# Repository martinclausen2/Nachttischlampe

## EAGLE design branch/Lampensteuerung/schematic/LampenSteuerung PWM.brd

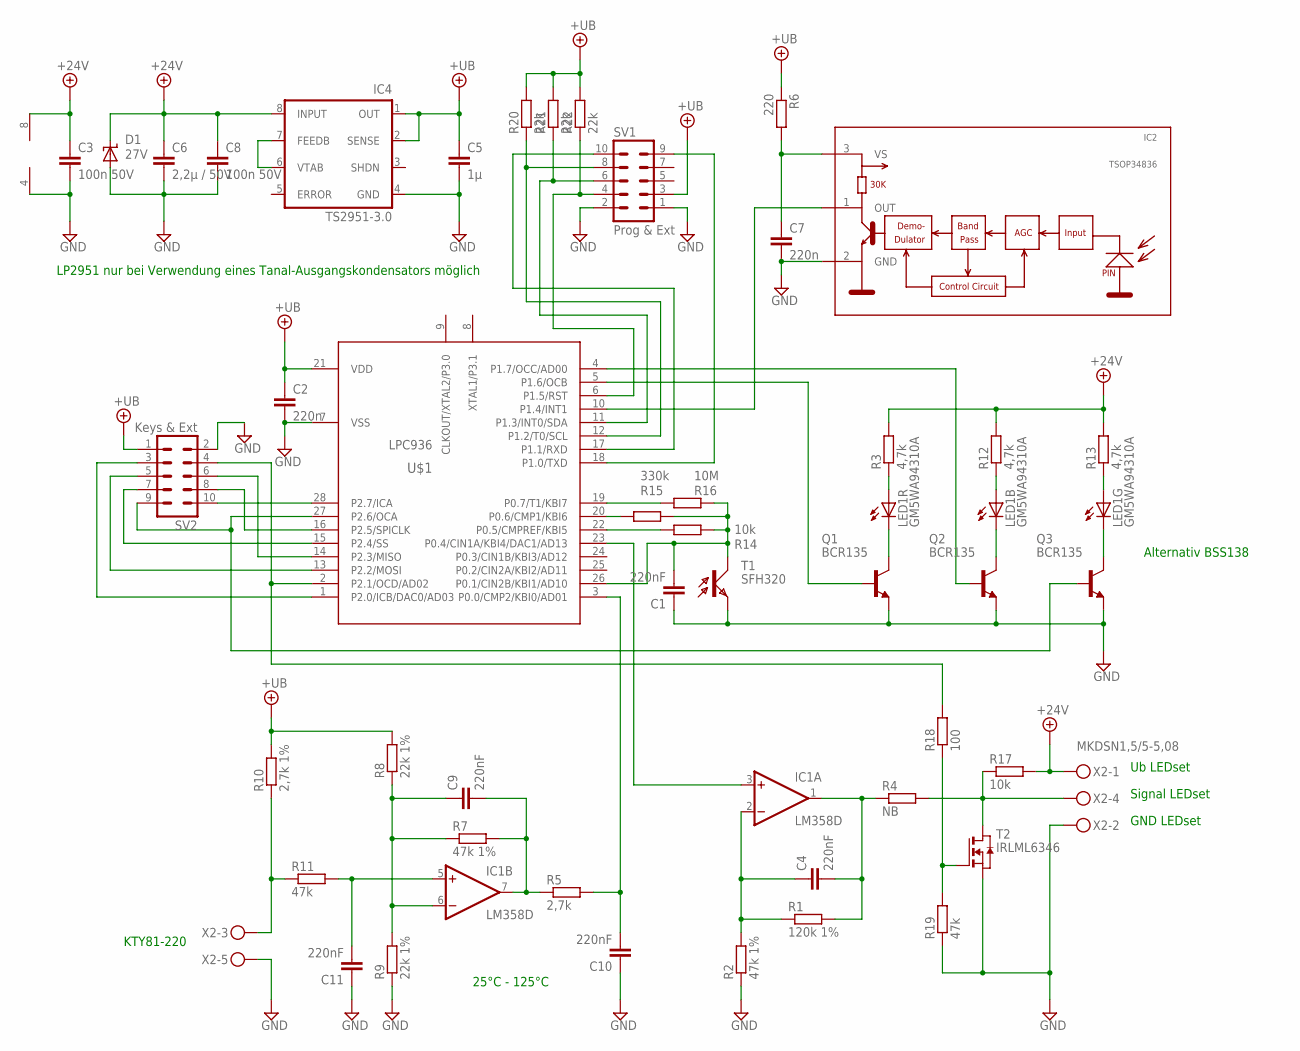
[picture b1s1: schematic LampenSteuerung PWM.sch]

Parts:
C1, C4, C9, C10, C11: 220nF; C0603
C2, C7: 220n; C0603
C3, C8: 100n 50V; C0603
C5: 1µ; C0805
C6: 2,2µ / 50V; C1206
D1: 27V; SMBJ
IC1: LM358D; SO08
IC2: TSOP34836; TSOP348
IC4: TS2951-3.0; SO-08
LED1: GM5WA94310A
Q1, Q2, Q3: BCR135; SOT23-BEC
R1: 120k 1%; R0805
R2, R7: 47k 1%; R0805
R3, R12, R13: 4,7k; R0805
R4: NB; R0805
R5: 2,7k; R0805
R6: 220; R0805
R8, R9: 22k 1%; R0805
R10: 2,7k 1%; R0805
R11, R19: 47k; R0805
R14, R17: 10k; R0805
R15: 330k; R0805
R16: 10M; R0805
R18: 100; R0805
R20, R21, R22: 22k; R0805
SV1: Prog & Ext; MA05-2
SV2: Keys & Ext; MA05-2
T1: SFH320; PLCC2
T2: IRLML6346; SOT-23
U$1: LPC936; TSSOP28
X2: MKDSN1,5/5-5,08

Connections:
+12V: C3.1, C6.1, C8.1, D1.C, IC1.8 (V+), IC4.8 (INPUT), R3.2, R12.2, R13.2, R17.2, X2.1
+UB: C2.1, C5.1, IC4.1 (OUT), IC4.2 (SENSE), R6.1, R8.2, R10.2, R20.2, R21.2, R22.2, SV1.3, SV2.1, U$1.21 (VDD)
GND: C1.1, C2.2, C3.2, C5.2, C6.2, C7.2, C8.2, C10.1, C11.1, D1.A, IC1.4 (V-), IC2.2 (GND), IC4.4 (GND), Q1.E, Q2.E, Q3.E, R2.1, R9.1, R19.1, SV1.1, SV1.2, SV2.2, T1.C (E), T2.2 (S), U$1.7 (VSS), X2.2, X2.5
unnamed: IC4.6 (VTAB), IC4.7 (FEEDB)
unnamed: IC2.1 (OUT), U$1.10 (P1.4/INT1)
unnamed: IC1.3 (+IN), U$1.23 (P0.4/CIN1A/KBI4/DAC1/AD13)
unnamed: C9.1, IC1.6 (-IN), R7.1, R8.1, R9.2
unnamed: LED1.5 (C), Q1.C
unnamed: C4.2, IC1.1 (OUT), R1.2, R4.1
unnamed: C4.1, IC1.2 (-IN), R1.1, R2.2
unnamed: SV1.10, U$1.17 (P1.1/RXD)
unnamed: R4.2, R17.1, T2.1 (D), X2.4
unnamed: C7.1, IC2.3 (VS), R6.2
unnamed: SV1.9, U$1.18 (P1.0/TXD)
unnamed: LED1.6 (C), Q2.C
unnamed: R22.1, SV1.4, U$1.6 (P1.5/RST)
unnamed: LED1.1 (A), R12.1
unnamed: R20.1, SV1.8, U$1.12 (P1.2/T0/SCL)
unnamed: R21.1, SV1.6, U$1.11 (P1.3/INT0/SDA)
unnamed: C10.2, R5.2, U$1.3 (P0.0/CMP2/KBI0/AD01)
unnamed: R10.1, R11.1, X2.3
unnamed: C9.2, IC1.7 (OUT), R5.1, R7.2
unnamed: C11.2, IC1.5 (+IN), R11.2
unnamed: LED1.2 (A), R3.1
unnamed: SV2.3, U$1.1 (P2.0/ICB/DAC0/AD03)
unnamed: R18.2, SV2.4, U$1.2 (P2.1/OCD/AD02)
unnamed: SV2.5, U$1.13 (P2.2/MOSI)
unnamed: SV2.6, U$1.14 (P2.3/MISO)
unnamed: SV2.7, U$1.15 (P2.4/SS)
unnamed: SV2.8, U$1.16 (P2.5/SPICLK)
unnamed: Q3.B, SV2.9, U$1.27 (P2.6/OCA)
unnamed: SV2.10, U$1.28 (P2.7/ICA)
unnamed: LED1.3 (A), R13.1
unnamed: LED1.4 (C), Q3.C
unnamed: Q1.B, U$1.5 (P1.6/OCB)
unnamed: Q2.B, U$1.4 (P1.7/OCC/AD00)
unnamed: C1.2, R14.1, R15.1, R16.1, T1.A (C), U$1.26 (P0.1/CIN2B/KBI1/AD10)
unnamed: R16.2, U$1.19 (P0.7/T1/KBI7)
unnamed: R15.2, U$1.20 (P0.6/CMP1/KBI6)
unnamed: R14.2, U$1.22 (P0.5/CMPREF/KBI5)
unnamed: R18.1, R19.2, T2.3 (G)

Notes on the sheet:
LP2951 nur bei Verwendung eines Tanal-Ausgangskondensators möglich
Signal LEDset
Ub LEDset
GND LEDset
KTY81-220
25°C - 125°C
Alternativ BSS138

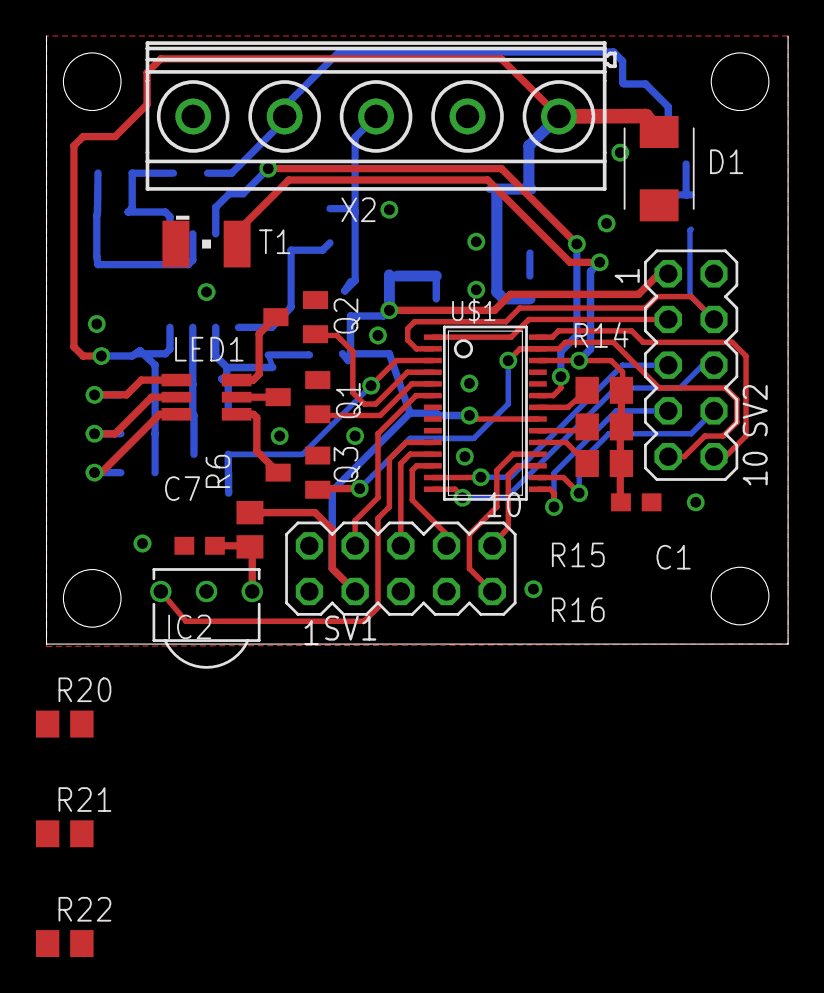
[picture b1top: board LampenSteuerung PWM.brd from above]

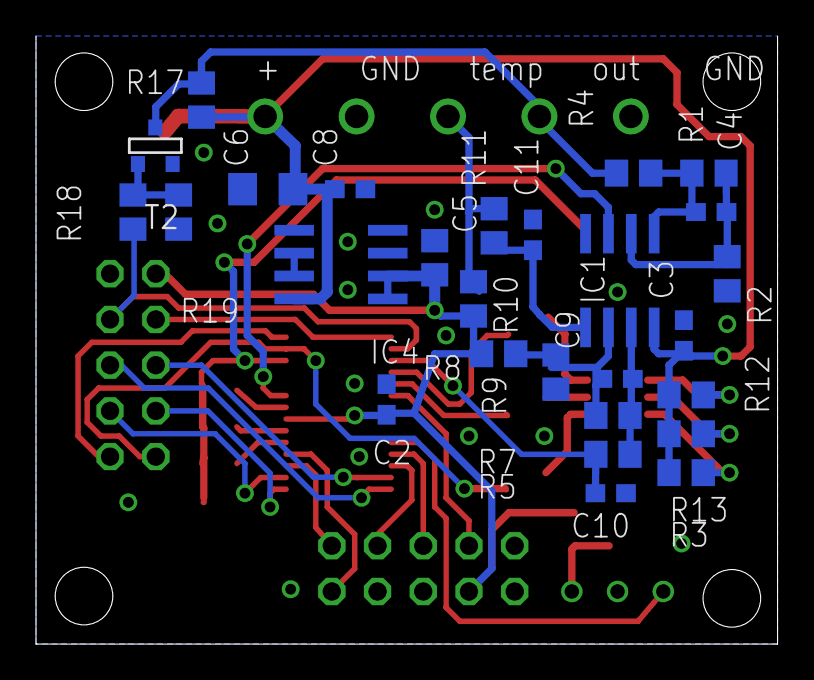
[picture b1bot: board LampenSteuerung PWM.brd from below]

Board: 2 copper layers, 41.2 x 33.8 mm, 47 parts (27 on the bottom side), 41 nets.

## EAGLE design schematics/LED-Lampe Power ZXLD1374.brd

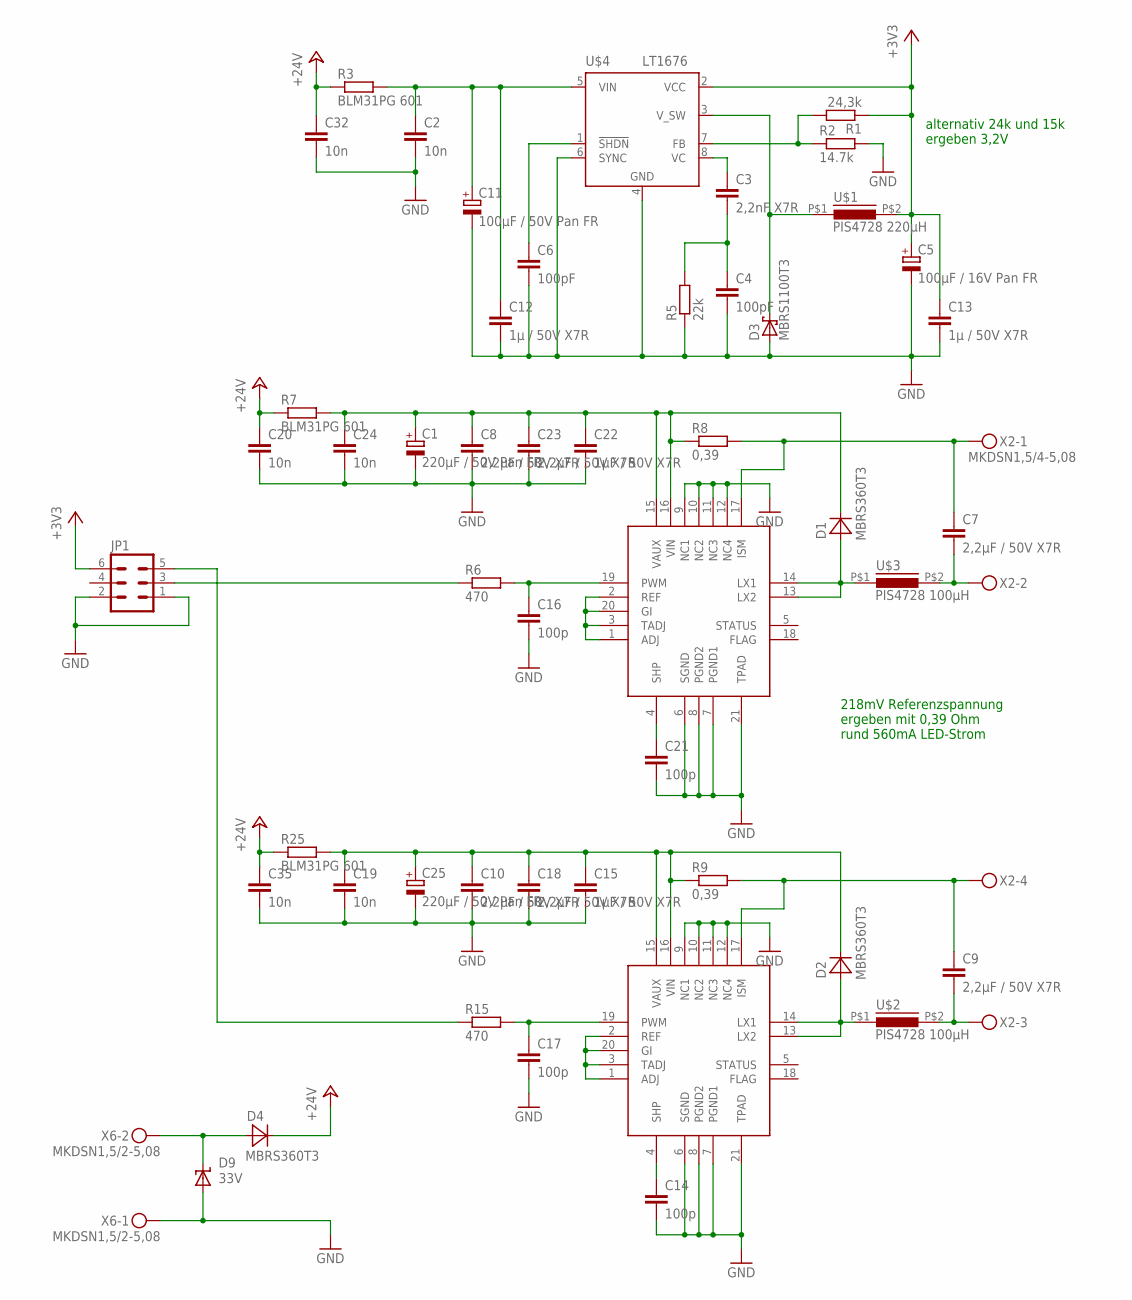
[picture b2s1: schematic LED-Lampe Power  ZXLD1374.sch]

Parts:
C1, C25: 220µF / 50V Pan FR; E5-10,5
C2, C19, C20, C24, C32, C35: 10n; C0805
C3: 2,2nF X7R; C0603
C4, C6: 100pF; C0603
C5: 100µF / 16V Pan FR; E2-5
C7, C8, C9, C10, C18, C23: 2,2µF / 50V X7R; C1206
C11: 100µF / 50V Pan FR; E3,5-8
C12, C13: 1µ / 50V X7R; C1206
C14, C16, C17, C21: 100p; C0603
C15, C22: 1µF / 50V X7R; C1206
D1, D2, D4: MBRS360T3; SMC
D3: MBRS1100T3; SMB
D9: 33V; SMBJ
JP1: ML6
R1: 24,3k; R1206
R2: 14.7k; R1206
R3, R7, R25: BLM31PG 601; R1206
R5: 22k; R1206
R6, R15: 470; R0805
R8, R9: 0,39; R1206
U$1: PIS4728 220µH; FASTON_PIS4728
U$2, U$3: PIS4728 100µH; FASTON_PIS4728
U$4: LT1676; S8
U$5, U$6: ZXLD1374; TSSOP20CA(FE)
X2: MKDSN1,5/4-5,08
X6: MKDSN1,5/2-5,08

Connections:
+3V3: C5.+, C13.1, JP1.6, R1.1, U$1.P$2 (2), U$4.2 (VCC); also elsewhere on the board
+24V: C20.1, C32.1, C35.1, D4.C, R3.1, R7.1, R25.1
GND: C1.-, C2.2, C4.2, C5.-, C6.2, C8.2, C10.2, C11.-, C12.2, C13.2, C14.2, C15.2, C16.2, C17.2, C18.2, C19.2, C20.2, C21.2, C22.2, C23.2, C24.2, C25.-, C32.2, C35.2, D3.A, D9.A, JP1.1, JP1.2, R2.2, R5.1, U$4.4 (GND), U$4.6 (SYNC), U$5.6 (SGND), U$5.7 (PGND1), U$5.8 (PGND2), U$5.9 (NC1), U$5.10 (NC2), U$5.11 (NC3), U$5.12 (NC4), U$5.21 (TPAD), U$6.6 (SGND), U$6.7 (PGND1), U$6.8 (PGND2), U$6.9 (NC1), U$6.10 (NC2), U$6.11 (NC3), U$6.12 (NC4), U$6.21 (TPAD), X6.1
unnamed: C2.1, C11.+, C12.1, R3.2, U$4.5 (VIN)
unnamed: U$5.1 (ADJ), U$5.2 (REF), U$5.3 (TADJ), U$5.20 (GI)
unnamed: C3.2, C4.1, R5.2
unnamed: R1.2, R2.1, U$4.7 (FB)
unnamed 7: D3.C, U$1.P$1 (1), U$4.3 (V_SW); also elsewhere on the board
unnamed: JP1.3, R6.1
unnamed: C1.+, C8.1, C22.1, C23.1, C24.1, D1.C, R7.2, R8.1, U$6.15 (VAUX), U$6.16 (VIN)
unnamed: D4.A, D9.C, X6.2
unnamed: C3.1, U$4.8 (VC)
unnamed 12: C9.2, U$2.P$2 (2), X2.3; also elsewhere on the board
unnamed: C17.1, R15.2, U$5.19 (PWM)
unnamed: C6.1, U$4.1 (!SHDN)
unnamed: C9.1, R9.2, U$5.17 (ISM), X2.4
unnamed: C14.1, U$5.4 (SHP)
unnamed 17: D2.A, U$2.P$1 (1), U$5.13 (LX2), U$5.14 (LX1); also elsewhere on the board
unnamed: C16.1, R6.2, U$6.19 (PWM)
unnamed 19: C7.2, U$3.P$2 (2), X2.2; also elsewhere on the board
unnamed: C7.1, R8.2, U$6.17 (ISM), X2.1
unnamed: U$6.1 (ADJ), U$6.2 (REF), U$6.3 (TADJ), U$6.20 (GI)
unnamed: C21.1, U$6.4 (SHP)
unnamed 23: D1.A, U$3.P$1 (1), U$6.13 (LX2), U$6.14 (LX1); also elsewhere on the board
unnamed: C10.1, C15.1, C18.1, C19.1, C25.+, D2.C, R9.1, R25.2, U$5.15 (VAUX), U$5.16 (VIN)
P1.6: JP1.5, R15.1

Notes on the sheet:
218mV Referenzspannung ergeben mit 0,39 Ohm rund 560mA LED-Strom
alternativ 24k und 15k ergeben 3,2V

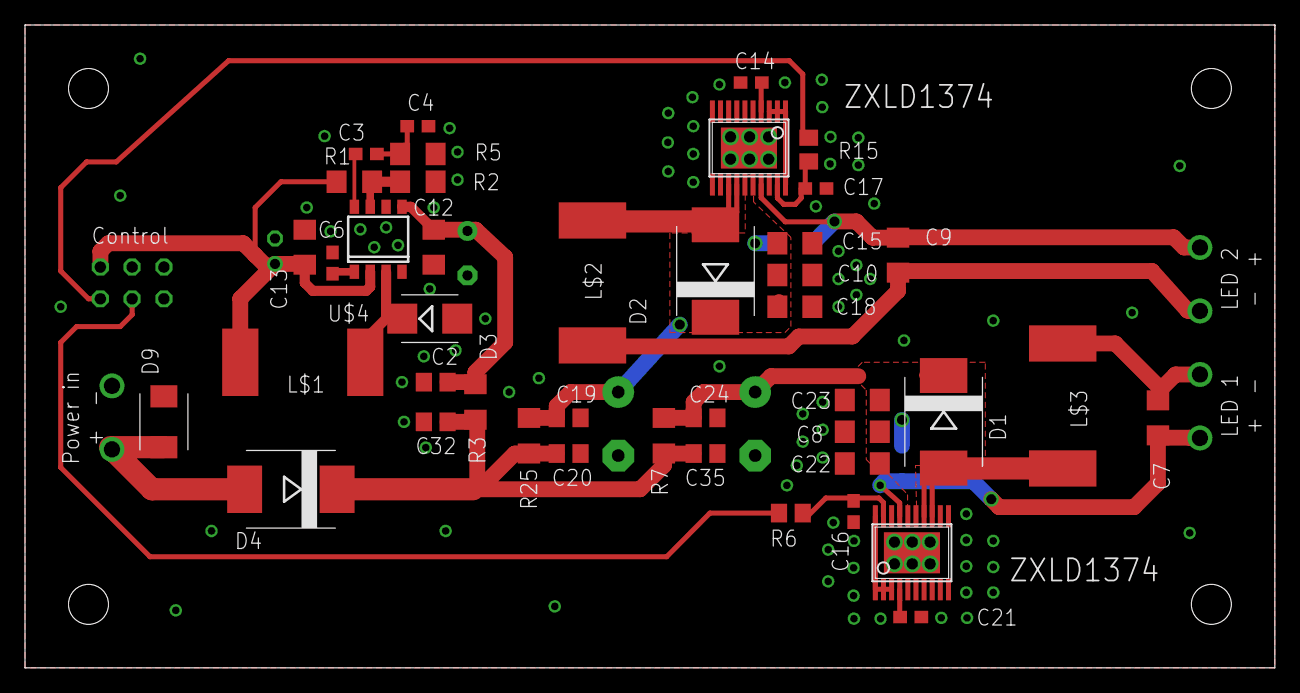
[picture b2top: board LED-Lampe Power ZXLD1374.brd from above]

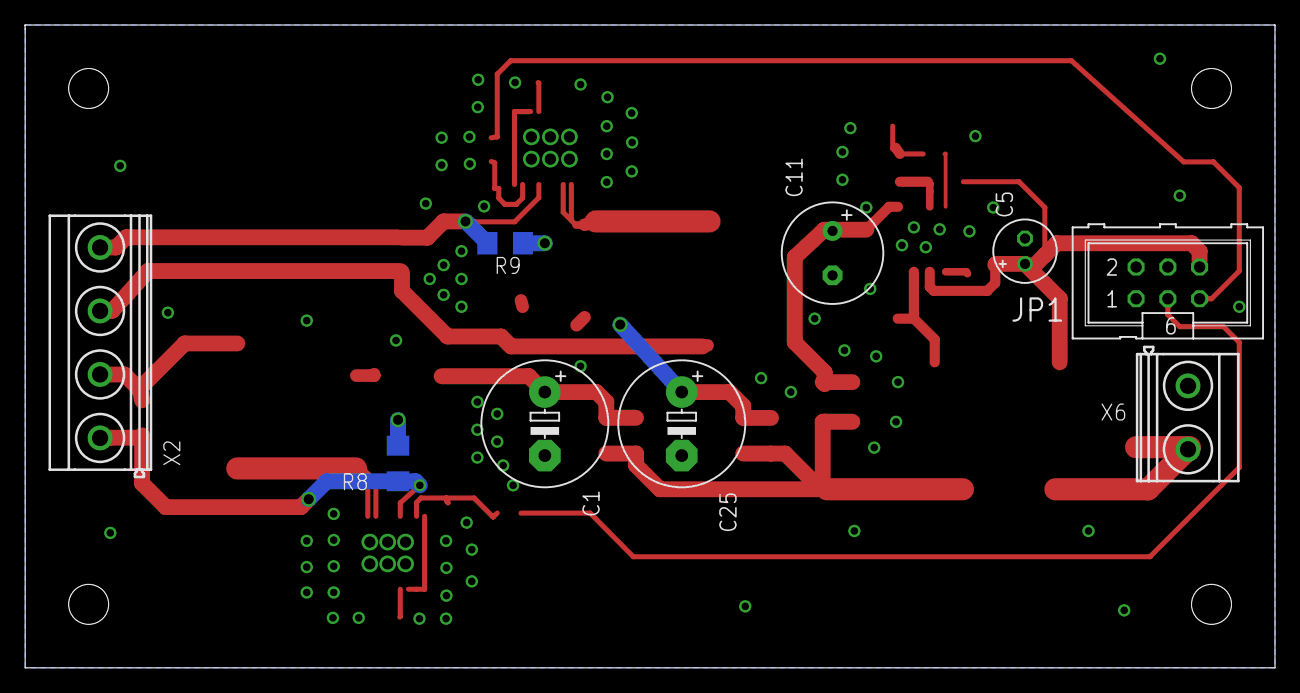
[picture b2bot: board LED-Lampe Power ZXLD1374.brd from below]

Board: 2 copper layers, 100.0 x 51.4 mm, 51 parts (9 on the bottom side), 26 nets.

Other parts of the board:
L$1: PIS4728 220µH; FASTON_PIS4728
L$2, L$3: PIS4728 100µH; FASTON_PIS4728

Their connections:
+3V3: L$1.P$2; also elsewhere on the board
unnamed 7: L$1.P$1; also elsewhere on the board
unnamed 12: L$2.P$2; also elsewhere on the board
unnamed 17: L$2.P$1; also elsewhere on the board
unnamed 19: L$3.P$2; also elsewhere on the board
unnamed 23: L$3.P$1; also elsewhere on the board

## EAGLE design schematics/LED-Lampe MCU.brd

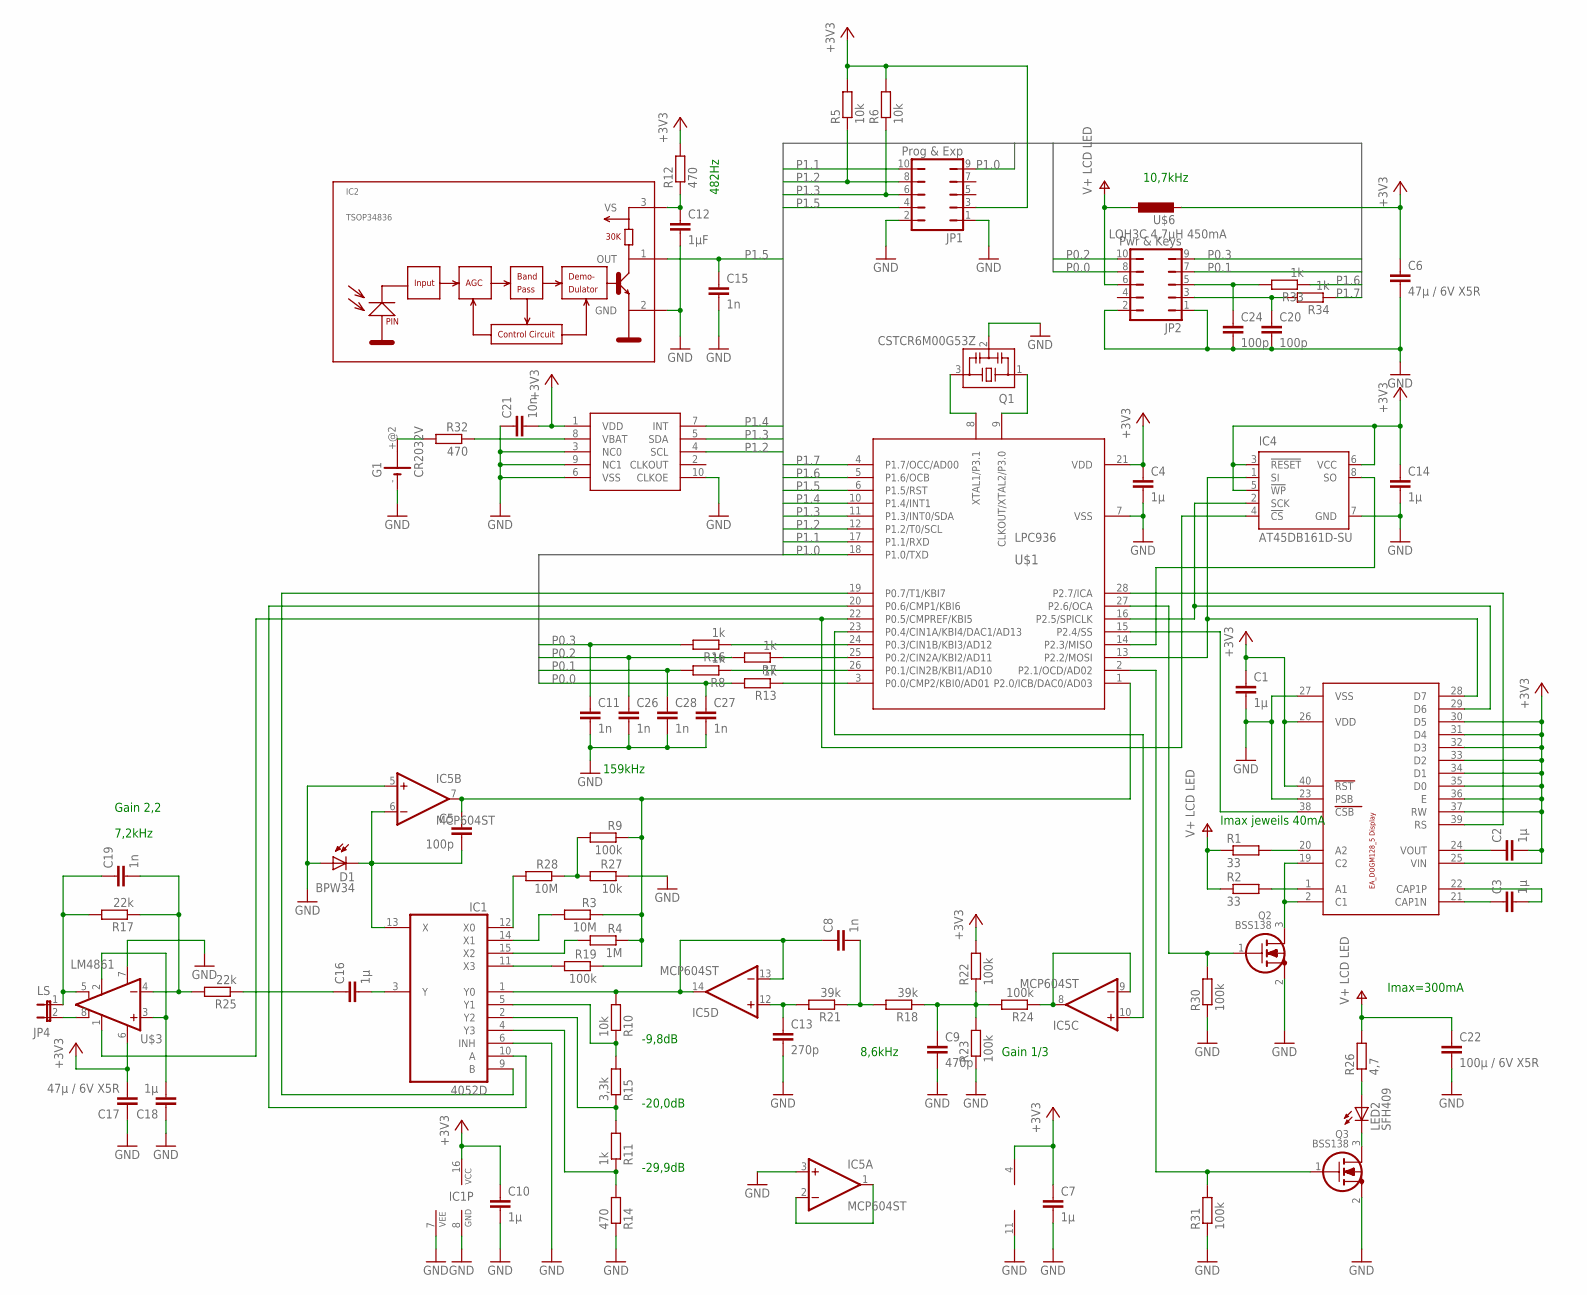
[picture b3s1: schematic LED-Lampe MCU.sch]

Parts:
C1, C2, C3, C4, C7, C10, C14: 1µ; C0805
C5, C20, C24: 100p; C0603
C6, C17: 47µ / 6V X5R; C1206
C8, C19: 1n; C0805
C9: 470p; C0805
C11, C15, C26, C27, C28: 1n; C0603
C12: 1µF; C0805
C13: 270p; C0805
C16, C18: 1µ; C1206
C21: 10n; C0805
C22: 100µ / 6V X5R; C1206
D1: BPW34; BPW32
G1: CR2032V
IC1: 4052D; SO16
IC2: TSOP34836; TSOP348
IC4: AT45DB161D-SU; 8S2
IC5: MCP604ST; TSSOP14
JP1: Prog & Exp; JP5Q
JP2: Pwr & Keys; JP5Q
JP4: LS; JP1
LED2: SFH409; LED3MM
Q1: CSTCR6M00G53Z; CSTCR6M
Q2, Q3: BSS138; SOT23
R1, R2: 33; R1206
R3, R28: 10M; R0805
R4: 1M; R0805
R5, R6, R10, R27: 10k; R0805
R7, R8, R11, R13, R16, R33, R34: 1k; R0805
R9, R19, R22, R23, R24, R30, R31: 100k; R0805
R12, R14, R32: 470; R0805
R15: 3,3k; R0805
R17, R25: 22k; R0805
R18, R21: 39k; R0805
R26: 4,7; R1206
U$1: LPC936; TSSOP28
U$2: EA_DOGM162; E_DOG-M162
U$3: LM4861; SO08
U$4: RV3029-C2; MC_RTC
U$6: LQH3C 4,7µH 450mA; L1210

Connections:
+3V3: C1.1, C2.2, C4.1, C6.1, C7.1, C10.1, C14.1, C17.2, C21.2, IC1.16 (VCC), IC4.3 (!RESET), IC4.5 (!WP), IC4.6 (VCC), IC5.4 (V+), JP1.3, R5.2, R6.2, R12.2, R22.2, U$1.21 (VDD), U$2.25 (VIN), U$2.26 (VDD), U$2.30 (D5), U$2.31 (D4), U$2.32 (D3), U$2.33 (D2), U$2.34 (D1), U$2.35 (D0), U$2.36 (E), U$2.37 (RW), U$2.40 (RST), U$3.6 (VDD), U$4.1 (VDD), U$6.2
GND: C1.2, C4.2, C6.2, C7.2, C9.2, C10.2, C11.2, C12.2, C13.2, C14.2, C15.2, C17.1, C18.1, C20.2, C21.1, C22.2, C24.2, C26.2, C27.2, C28.2, D1.A, G1.-, IC1.6 (INH), IC1.7 (VEE), IC1.8 (GND), IC2.2 (GND), IC4.7 (GND), IC5.3 (+IN), IC5.5 (+IN), IC5.11 (V-), JP1.1, JP1.2, JP2.1, JP2.2, Q1.2, Q2.2 (S), Q3.2 (S), R14.1, R23.1, R27.1, R30.1, R31.1, U$1.7 (VSS), U$2.23 (PSB), U$2.27 (VSS), U$3.7 (GND), U$4.3 (NC0), U$4.6 (VSS), U$4.9 (NC1), U$4.10 (CLKOE)
unnamed: C2.1, U$2.24 (VOUT)
unnamed: IC1.9 (B), U$1.19 (P0.7/T1/KBI7)
unnamed: C3.2, U$2.22 (CAP1P)
unnamed: C3.1, U$2.21 (CAP1N)
unnamed: U$1.15 (P2.4/SS), U$2.38 (CSB)
unnamed: C12.1, IC2.3 (VS), R12.1
unnamed: R1.2, U$2.20 (A2)
unnamed: R2.2, U$2.1 (A1)
unnamed: IC4.2 (SCK), U$1.16 (P2.5/SPICLK), U$2.29 (D6)
unnamed: IC4.1 (SI), U$1.13 (P2.2/MOSI), U$2.28 (D7)
unnamed: Q2.1 (G), R30.2, U$1.27 (P2.6/OCA)
unnamed: IC1.10 (A), U$1.20 (P0.6/CMP1/KBI6)
unnamed: U$1.28 (P2.7/ICA), U$2.39 (RS)
unnamed: Q1.3, U$1.8 (XTAL1/P3.1)
unnamed: Q1.1, U$1.9 (CLKOUT/XTAL2/P3.0)
unnamed: Q2.3 (D), U$2.2 (C1), U$2.19 (C2)
unnamed: R8.1, U$1.26 (P0.1/CIN2B/KBI1/AD10)
unnamed: JP4.2, U$3.8 (VO2)
unnamed: R16.1, U$1.24 (P0.3/CIN1B/KBI3/AD12)
unnamed: R13.1, U$1.3 (P0.0/CMP2/KBI0/AD01)
unnamed: C18.2, U$3.2 (BYPASS), U$3.3 (+IN)
unnamed: R7.1, U$1.25 (P0.2/CIN2A/KBI2/AD11)
unnamed: IC4.8 (SO), U$1.14 (P2.3/MISO)
unnamed: IC1.4 (Y3), R11.1, R14.2
unnamed: IC1.2 (Y2), R11.2, R15.1
unnamed: IC1.5 (Y1), R10.1, R15.2
unnamed: C8.1, IC1.1 (Y0), IC5.13 (-IN), IC5.14 (OUT), R10.2
unnamed: C13.1, IC5.12 (+IN), R21.2
unnamed: C8.2, R18.2, R21.1
unnamed: LED2.A, R26.1
unnamed: IC5.10 (+IN), U$1.23 (P0.4/CIN1A/KBI4/DAC1/AD13)
unnamed: C5.2, D1.K (C), IC1.13 (X), IC5.6 (-IN)
unnamed: C5.1, IC5.7 (OUT), R3.1, R4.1, R9.1, R19.1, U$1.1 (P2.0/ICB/DAC0/AD03)
unnamed: IC1.11 (X3), R19.2
unnamed: C9.1, R18.1, R22.1, R23.2, R24.2
unnamed: Q3.1 (G), R31.2, U$1.2 (P2.1/OCD/AD02)
unnamed: IC1.15 (X2), R4.2
unnamed: IC1.14 (X1), R3.2
unnamed: IC1.12 (X0), R28.2
unnamed: C19.2, R17.1, R25.2, U$3.4 (-IN)
unnamed: C16.1, R25.1
unnamed: C16.2, IC1.3 (Y)
unnamed: C19.1, JP4.1, R17.2, U$3.5 (VO1)
unnamed: LED2.K (C), Q3.3 (D)
unnamed: IC4.4 (!CS), U$1.22 (P0.5/CMPREF/KBI5), U$3.1 (SHUTDOWN)
unnamed: R32.1, U$4.8 (VBAT)
unnamed: R9.2, R27.2, R28.1
unnamed: IC5.8 (OUT), IC5.9 (-IN), R24.1
unnamed: G1.+@2 (+), R32.2
unnamed: IC5.1 (OUT), IC5.2 (-IN)
unnamed: C24.1, JP2.5, R33.2
unnamed: C20.1, JP2.3, R34.2
P0.0: C27.1, JP2.8, R13.2
P0.1: C28.1, JP2.7, R8.2
P0.2: C26.1, JP2.10, R7.2
P0.3: C11.1, JP2.9, R16.2
P1.0: JP1.9, U$1.18 (P1.0/TXD)
P1.1: JP1.10, U$1.17 (P1.1/RXD)
P1.2: JP1.8, R5.1, U$1.12 (P1.2/T0/SCL), U$4.4 (SCL)
P1.3: JP1.6, R6.1, U$1.11 (P1.3/INT0/SDA), U$4.5 (SDA)
P1.4: U$1.10 (P1.4/INT1), U$4.7 (INT)
P1.5: C15.1, IC2.1 (OUT), JP1.4, U$1.6 (P1.5/RST)
P1.6: R33.1, U$1.5 (P1.6/OCB)
P1.7: R34.1, U$1.4 (P1.7/OCC/AD00)
V+: C22.1, JP2.6, R1.1, R2.1, R26.2, U$6.1

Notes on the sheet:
10,7kHz
482Hz
159kHz
8,6kHz
Gain 1/3
Gain 2,2
7,2kHz
Imax=300mA
-9,8dB
-20,0dB
-29,9dB
Imax jeweils 40mA

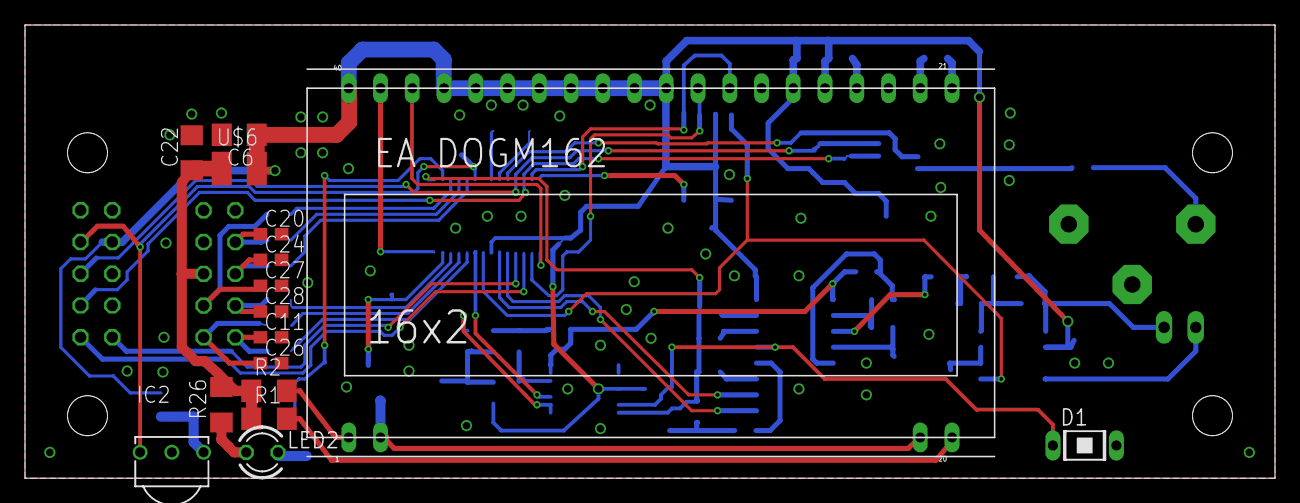
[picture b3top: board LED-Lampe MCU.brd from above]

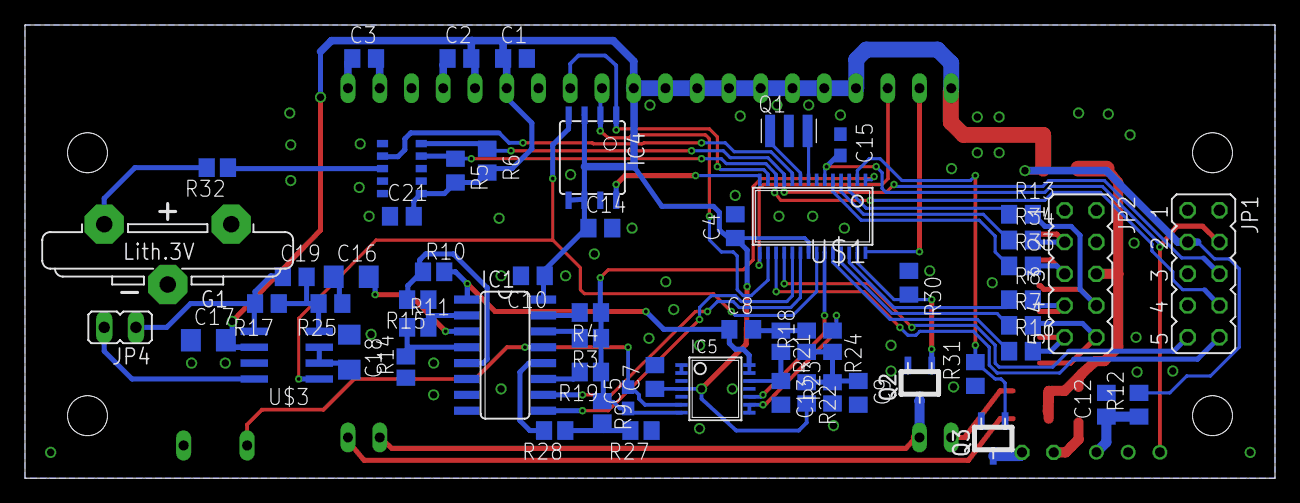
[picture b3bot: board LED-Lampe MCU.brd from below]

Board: 2 copper layers, 100.0 x 36.3 mm, 76 parts (60 on the bottom side), 67 nets.

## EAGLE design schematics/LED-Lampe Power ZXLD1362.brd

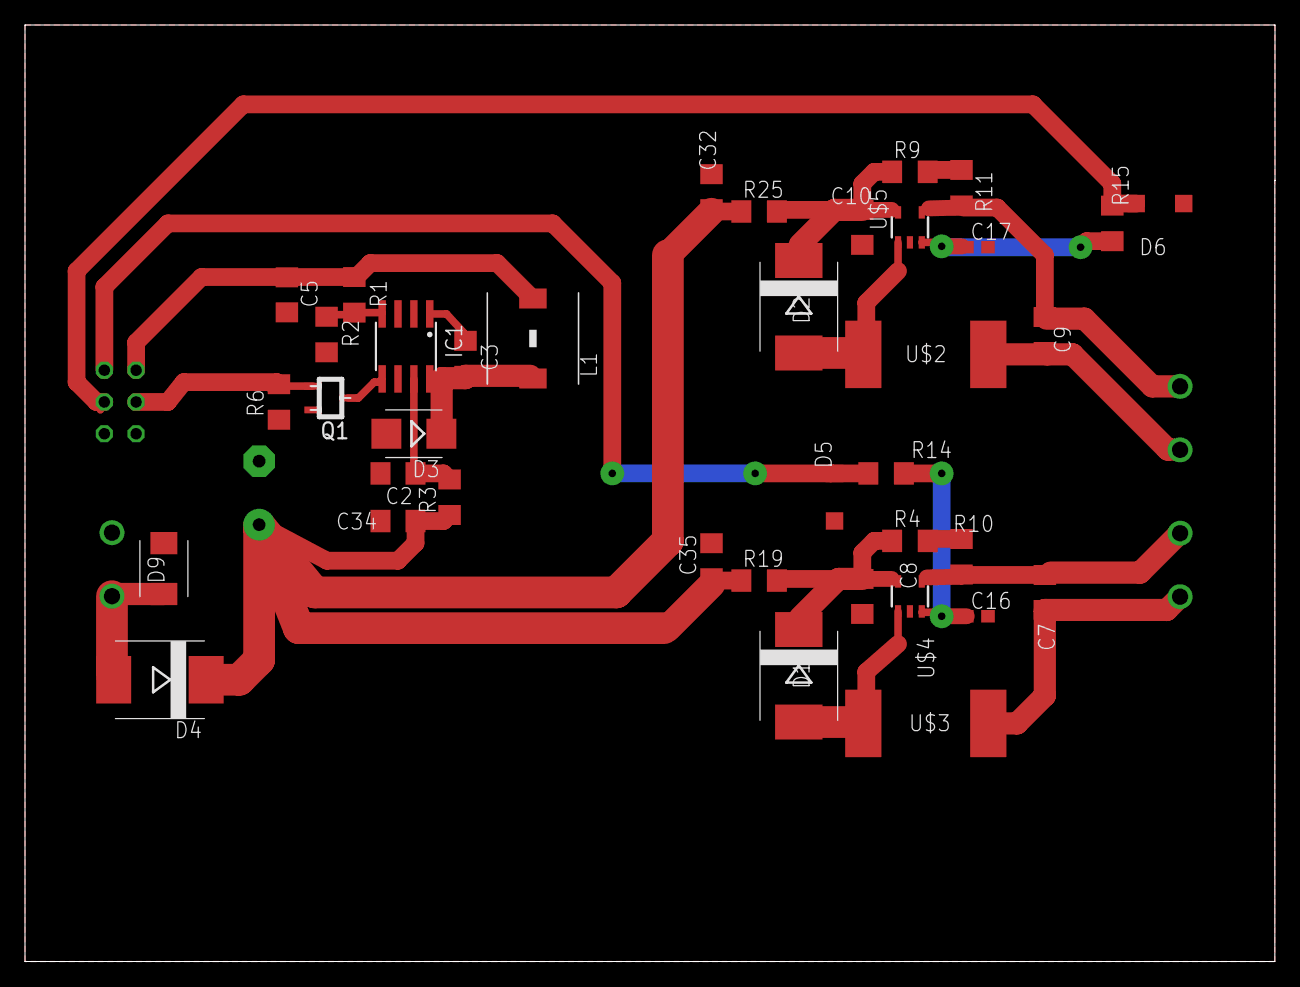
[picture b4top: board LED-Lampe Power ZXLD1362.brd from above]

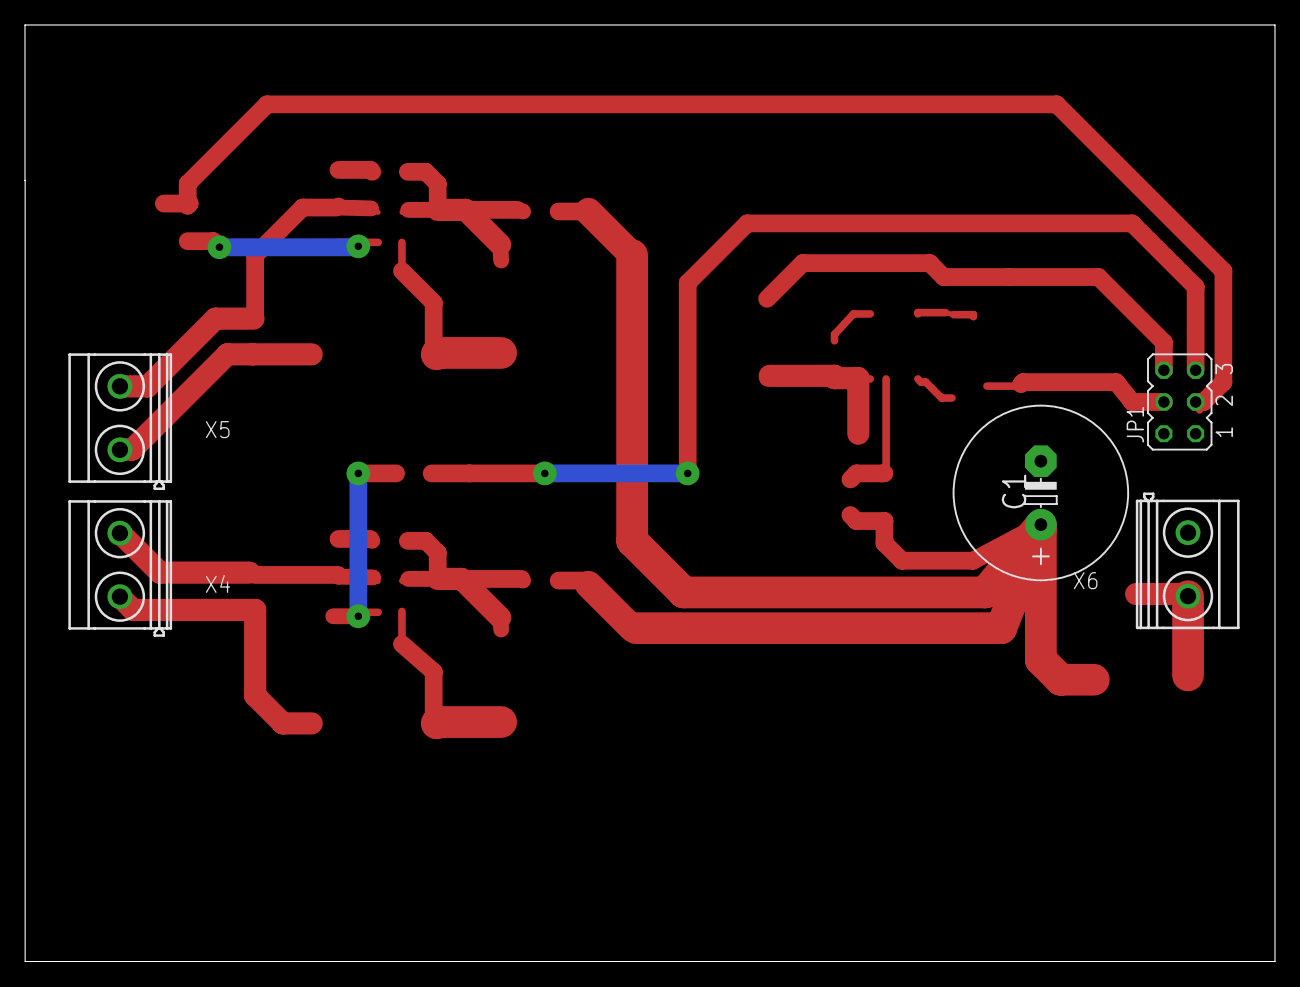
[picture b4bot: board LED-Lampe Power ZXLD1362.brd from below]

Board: 2 copper layers, 100.0 x 74.9 mm, 43 parts (5 on the bottom side), 24 nets.

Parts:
C1: 470µ / 35V; E5-13
C2, C8, C10: 4,7µ / 50V X7R; C1206
C3, C32, C34, C35: 10n; C1206
C5: 47µ / 6V X5R; C1206
C7, C9: 1µF / 50V X7R; C1206
C16, C17: 100p; C0603
D1, D2, D4: MBRS360T3; SMC
D3: MBRS140T3; SMB
D5, D6: L103; SOD123
D9: 33V; SMBJ
IC1: LM2671M; SO08
JP1: JP3Q
L1: WE-PD_S/M 220µH 300mA; WE-PD_S/M
Q1: BSS138; SOT23
R1: 3,9k; R1206
R2: 2,2k; R1206
R3, R19, R25: BLM31PG 601; R1206
R4, R9, R10, R11: 0,1; R1206
R6: 10k; R1206
R14, R15: 2,4k; R1206
U$2, U$3: FASTON_PIS4728 68µH; FASTON_PIS4728
U$4, U$5: ZXLD1362; SOT23-5
X4, X5, X6: MKDSN1,5/2-5,08

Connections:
+3V3: C5.1, JP1.6, L1.2, R1.1
+24V: C1.+, C32.1, C34.1, C35.1, D4.C, R3.1, R19.1, R25.1
GND: C1.-, C2.2, C5.2, C8.2, C10.2, C16.2, C17.2, C32.2, C34.2, C35.2, D3.A, D5.A, D6.A, D9.A, IC1.6, JP1.1, JP1.2, Q1.2, R2.2, R6.1, U$4.2, U$5.2, X6.1
unnamed: C2.1, IC1.7, R3.2
unnamed: C3.1, IC1.1
unnamed: IC1.4, R1.2, R2.1
unnamed: C3.2, D3.C, IC1.8, L1.1
unnamed: JP1.4, Q1.1, R6.2
unnamed: R4.2, R10.1
unnamed: R9.2, R11.1
unnamed: D4.A, D9.C, X6.2
unnamed: C16.1, R14.2, U$4.3
unnamed: IC1.5, Q1.3
unnamed: C17.1, R15.2, U$5.3
unnamed: D1.A, U$3.P$1, U$4.1
unnamed: C7.1, U$3.P$2, X4.1
unnamed: C7.2, R10.2, U$4.4, X4.2
unnamed: D2.A, U$2.P$1, U$5.1
unnamed: C9.1, U$2.P$2, X5.1
unnamed: C9.2, R11.2, U$5.4, X5.2
unnamed: C8.1, D1.C, R4.1, R19.2, U$4.5
unnamed: C10.1, D2.C, R9.1, R25.2, U$5.5
P1.6: D6.C, JP1.3, R15.1
P1.7: D5.C, JP1.5, R14.1

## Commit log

2013-10-11 Initial Upload
2013-10-11 added schematics and PCB added mechanics
2013-10-11 first stable upload
2013-10-17 - finalized layout - moved to eagle 6.5
2013-11-03 - added dynamic PWM frequency selection - extended options menu by brightness offset and min brightness - increased dimming frequency to 40Hz
2013-11-03 - fix ZXLD1374 case
2013-12-09 - added fill & 2nd line function to lcd driver => code clean-up - added user feedback on key pressed - fixed missing pause between IR commands in all go standby - added fade in to snooze end menu - p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
2013-12-09 - minor code clean-up
2014-02-03 - add: option to cancel key press - add: optional acoustic signal to acknowledge key press - add: ZXLD1374 support via compiler switch
2014-02-05 -fix: missing key acknowledge
2014-02-22 - changed to LED driver ZXLD1374 as a default - fixed output configuration of PWM Pins - added "sample beep" during beep volume adjustment, fixed volume enumeration
2014-03-10 - improved placement of IR-LED, IR-Receiver, Photodiode - removed unused devices
2014-03-11 added 3D-model of mechanics for left and right lamp and description
2014-09-04 filled Lampensteuerung branch
2014-09-07 added motion detector signal handling added LCD option via #define
2014-09-07 fix alarm
2014-09-07 fix spelling fix time out for acoustic alarm
2014-09-12 fix missing off slope at analogue output fix spike during analogue output on fix timing
2014-09-14 added time slots for main loop fixed timing other small fixes
2014-09-14 fix comment
2014-09-16 fix inverted PWM output
2014-10-08 fixed missing offset for output cleaned RC5 code, added function for number buttons fixed comments
2014-10-09 reduce power consumption of MCU
2014-10-12 add remote control number block functionality code clean-up
2015-04-06 fixed display error
2015-05-18 added missing pull-up resistors added wire pads for output shifted some components slightly to ease mounting
2015-09-24 - option to compile for noninverted PWM output for direct drive of LEDs - flash LED if brightness limits are reached - added comments, fixed spelling
2015-09-25 - fixed led min max led flash - increased encoder acceleration
2015-10-01 - optimize encoder settings - fix limit led signal in options
2015-10-01 - optimize encoder settings further
2015-10-03 - fixed flicker of output - fixed overflow in Encoder.c - use lower limit instead of zero for brightness
2015-10-03 - fix lower limit for brightness
2015-10-05 - added version for direct PWM control
2016-03-12 add mechanics and schematics
2021-03-28 adjust ADC settings for more precise ambient light measurement
